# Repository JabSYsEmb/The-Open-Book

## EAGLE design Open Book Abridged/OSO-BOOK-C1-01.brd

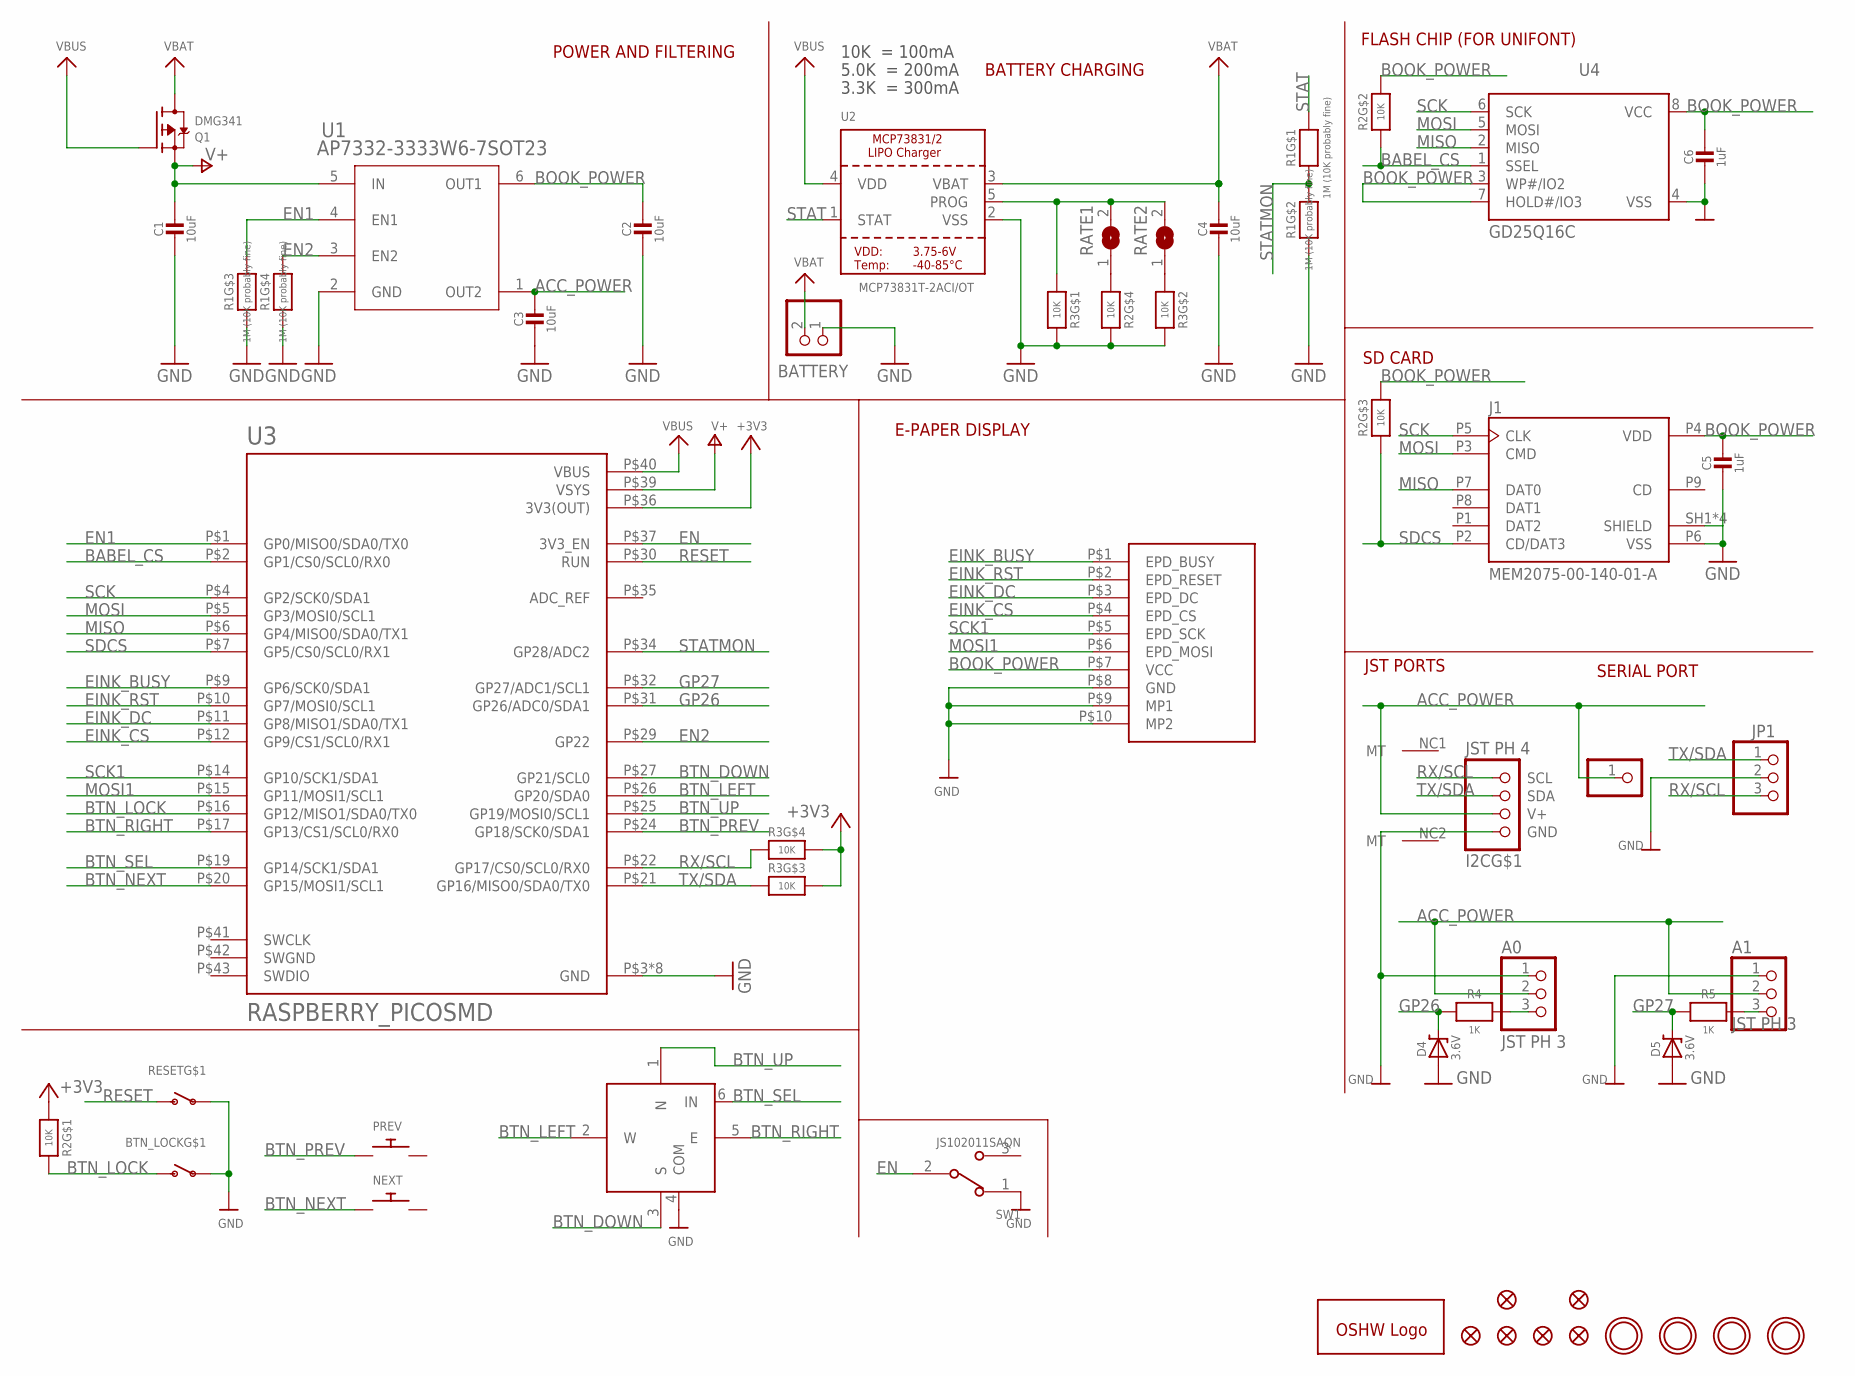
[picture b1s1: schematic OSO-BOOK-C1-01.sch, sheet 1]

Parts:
A0, A1: JST PH 3; JSTPH3
BATTERY: JSTPH; JSTPH2
BTN_LOCK: SWITCH_SPSTTL3330A; TL3330A
C1, C2, C3, C4: 10uF; 0805-NO
C5, C6: 1uF; 0805-NO
D4, D5: 3.6V; SOD-123
FID1, FID2, FID3, FID4, FID5, FID6: FIDUCIAL_1MM
GOLD_ORB_SM1: OSHWLOGOLOGO5MM; OSHW_5MM
I2C: JST PH 4; JSTPH4
J1: MEM2075-00-140-01-A; GCT_MEM2075-00-140-01-A
JP1: PINHD-1X3; 1X03
JP2: PINHD-1X1; 1X01
NEXT: SWITCH_PUSHBUTTON_3.5X6MM; TACTILE_3X6MM
PREV: SWITCH_PUSHBUTTON_3.5X6MM; TACTILE_3X6MM
Q1: DMG341; SOT23-R
R1: 1M (10K probably fine); EXBV8V
R2, R3: 10K; EXBV8V
R4, R5: 1K; 0805-NO
RATE1, RATE2: SOLDERJUMPER; SOLDERJUMPER_ARROW_NOPASTE
RESET: SWITCH_SPSTTL3330A; TL3330A
SW1: JS102011SAQN; SW_JS102011SAQN
SW2: NAVSWITCHSKQUABAUE010; SKQUBAE010
U1: AP7332-3333W6-7SOT23; SOT23-6
U2: MCP73831T-2ACI/OT; SOT23-5
U3: RASPBERRY_PICOSMD; PICO-PKG-SMD
U4: GD25Q16C; MICROBUILDER_SOIC8_150MIL
U$1, U$4, U$5, U$7: MOUNTINGHOLE2.5; MOUNTINGHOLE_2.5_PLATED
U$11: OSO-BOOK-C2-01

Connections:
+3V3: R2.1, R3.5 (2), R3.6 (2), U3.P$36 (3V3(OUT))
ACC_POWER: A0.2, A1.2, C3.1, I2C.2 (V+), JP2.1, U1.1 (OUT2)
BABEL_CS: R2.2 (1), U3.P$2 (GP1/CS0/SCL0/RX0), U4.1 (SSEL)
BOOK_POWER: C2.1, C5.1, C6.1, J1.P4 (VDD), R2.6 (2), R2.7 (2), U1.6 (OUT1), U4.3 (WP#/IO2), U4.7 (HOLD#/IO3), U4.8 (VCC), U$11.P$7 (VCC)
BTN_DOWN: SW2.3 (S), U3.P$27 (GP21/SCL0)
BTN_LEFT: SW2.2 (W), U3.P$26 (GP20/SDA0)
BTN_LOCK: BTN_LOCK.P$2 (S), R2.8 (2), U3.P$16 (GP12/MISO1/SDA0/TX0)
BTN_NEXT: NEXT.P$1, U3.P$20 (GP15/MOSI1/SCL1)
BTN_PREV: PREV.P$1, U3.P$24 (GP18/SCK0/SDA1)
BTN_RIGHT: SW2.5 (E), U3.P$17 (GP13/CS1/SCL0/RX0)
BTN_SEL: SW2.6 (IN), U3.P$19 (GP14/SCK1/SDA1)
BTN_UP: SW2.1 (N), U3.P$25 (GP19/MOSI0/SCL1)
EINK_BUSY: U3.P$9 (GP6/SCK0/SDA1), U$11.P$1 (EPD_BUSY)
EINK_CS: U3.P$12 (GP9/CS1/SCL0/RX1), U$11.P$4 (EPD_CS)
EINK_DC: U3.P$11 (GP8/MISO1/SDA0/TX1), U$11.P$3 (EPD_DC)
EINK_RST: U3.P$10 (GP7/MOSI0/SCL1), U$11.P$2 (EPD_RESET)
EN: SW1.2, U3.P$37 (3V3_EN)
EN1: R1.3 (1), U1.4 (EN1), U3.P$1 (GP0/MISO0/SDA0/TX0)
EN2: R1.4 (1), U1.3 (EN2), U3.P$29 (GP22)
GND: A0.1, A1.1, BATTERY.1, BTN_LOCK.P$1, C1.2, C2.2, C3.2, C4.2, C5.2, C6.2, D4.A, D5.A, I2C.1 (GND), J1.P6 (VSS), J1.SH1 (SHIELD), J1.SH2 (SHIELD), J1.SH3 (SHIELD), J1.SH4 (SHIELD), JP1.2, R1.2 (1), R1.5 (2), R1.6 (2), R2.5 (2), R3.7 (2), R3.8 (2), RESET.P$1, SW1.1, SW2.4 (COM), U1.2 (GND), U2.2 (VSS), U3.P$3 (GND), U3.P$8 (GND), U3.P$13 (GND), U3.P$18 (GND), U3.P$23 (GND), U3.P$28 (GND), U3.P$33 (GND), U3.P$38 (GND), U4.4 (VSS), U$11.P$8 (GND), U$11.P$9 (MP1), U$11.P$10 (MP2)
GP26: D4.C, R4.2, U3.P$31 (GP26/ADC0/SDA1)
GP27: D5.C, R5.2, U3.P$32 (GP27/ADC1/SCL1)
MISO: J1.P7 (DAT0), U3.P$6 (GP4/MISO0/SDA0/TX1), U4.2 (MISO)
MOSI: J1.P3 (CMD), U3.P$5 (GP3/MOSI0/SCL1), U4.5 (MOSI)
MOSI1: U3.P$15 (GP11/MOSI1/SCL1), U$11.P$6 (EPD_MOSI)
unnamed: R2.4 (1), RATE1.1
unnamed: R3.2 (1), RATE2.1
PROG: R3.1, RATE1.2, RATE2.2, U2.5 (PROG)
RESET: RESET.P$2 (S), U3.P$30 (RUN)
RX/SCL: I2C.4 (SCL), JP1.3, R3.4 (1), U3.P$22 (GP17/CS0/SCL0/RX0)
SCK: J1.P5 (CLK), U3.P$4 (GP2/SCK0/SDA1), U4.6 (SCK)
SCK1: U3.P$14 (GP10/SCK1/SDA1), U$11.P$5 (EPD_SCK)
SDCS: J1.P2 (CD/DAT3), R2.3 (1), U3.P$7 (GP5/CS0/SCL0/RX1)
STAT: R1.8 (2), U2.1 (STAT)
STATMON: R1.1, R1.7 (2), U3.P$34 (GP28/ADC2)
SWGND: U3.P$42 (SWGND)
TX/SDA: I2C.3 (SDA), JP1.1, R3.3 (1), U3.P$21 (GP16/MISO0/SDA0/TX0)
V+: C1.1, Q1.2 (S), U1.5 (IN), U3.P$39 (VSYS)
VBAT: BATTERY.2, C4.1, Q1.3 (D), U2.3 (VBAT)
VBUS: Q1.1 (G), U2.4 (VDD), U3.P$40 (VBUS)
_GP26: A0.3, R4.1
_GP27: A1.3, R5.1

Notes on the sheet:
POWER AND FILTERING
10K = 100mA
5.0K = 200mA
3.3K = 300mA
BATTERY CHARGING
FLASH CHIP (FOR UNIFONT)
SERIAL PORT
JST PORTS
SD CARD
E-PAPER DISPLAY

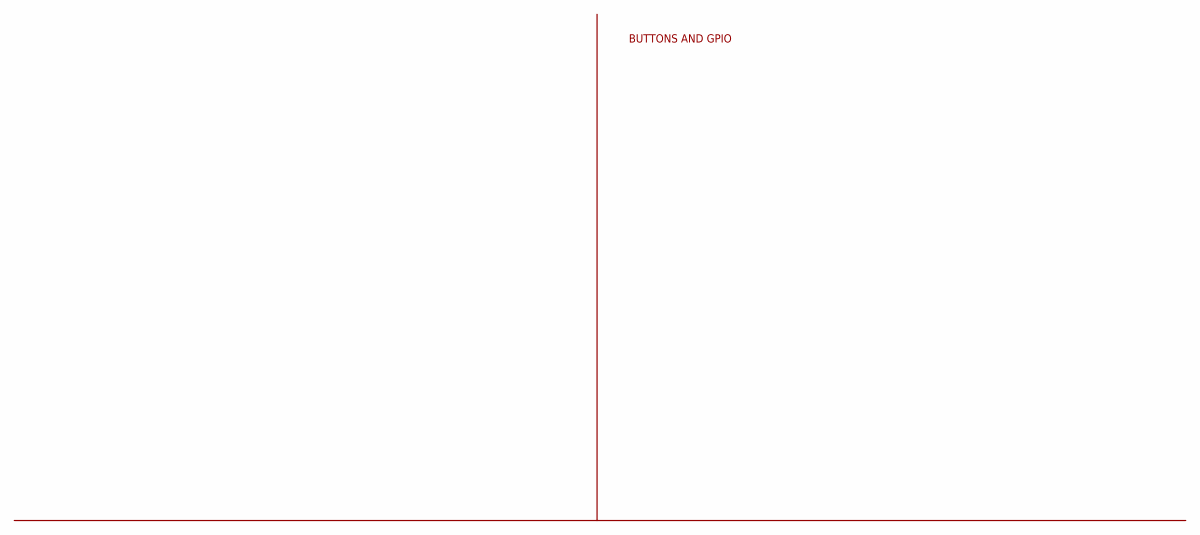
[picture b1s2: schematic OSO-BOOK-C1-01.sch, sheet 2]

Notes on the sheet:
BUTTONS AND GPIO

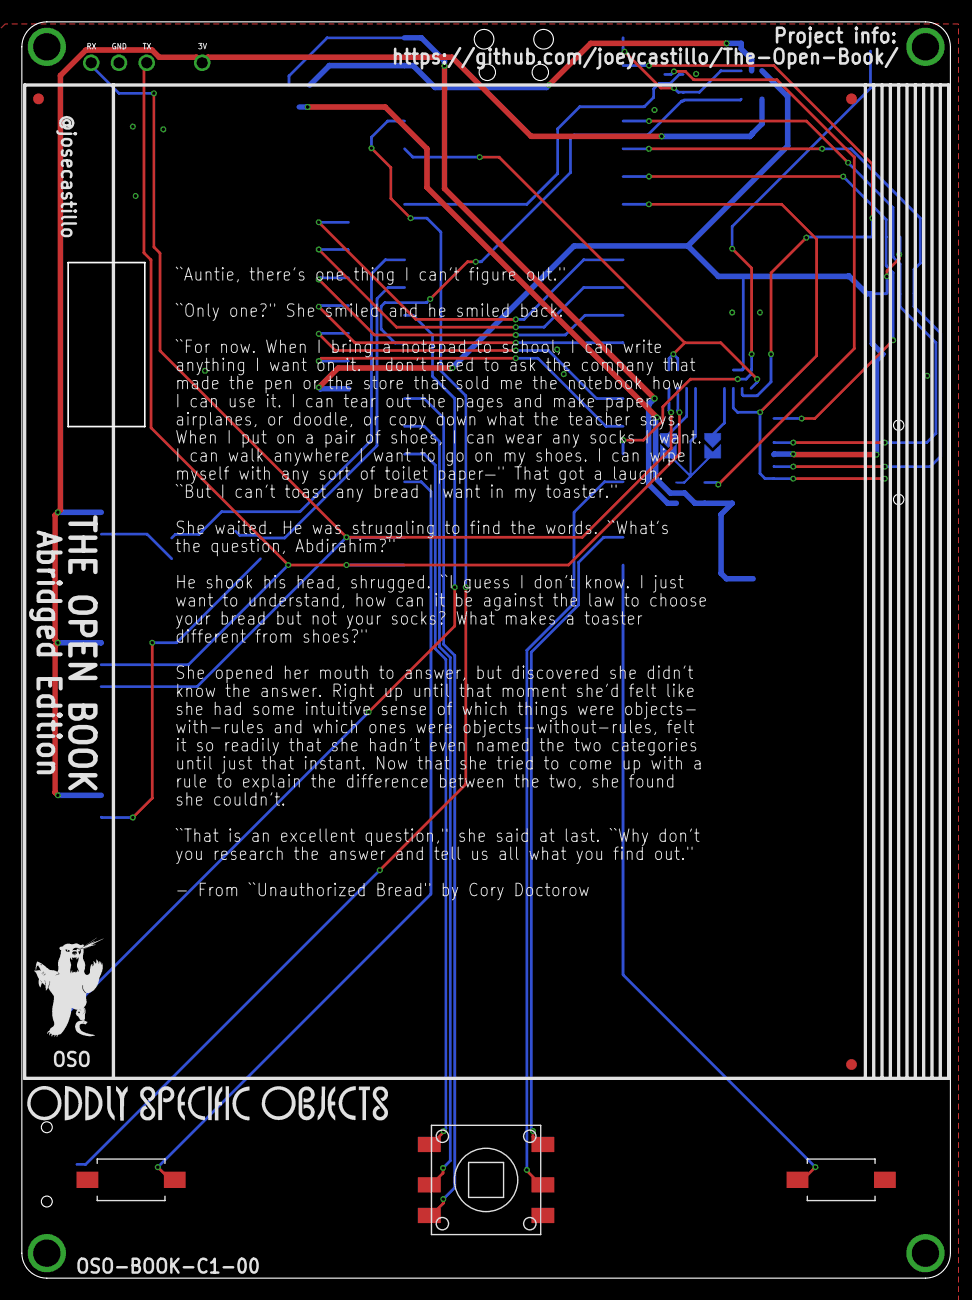
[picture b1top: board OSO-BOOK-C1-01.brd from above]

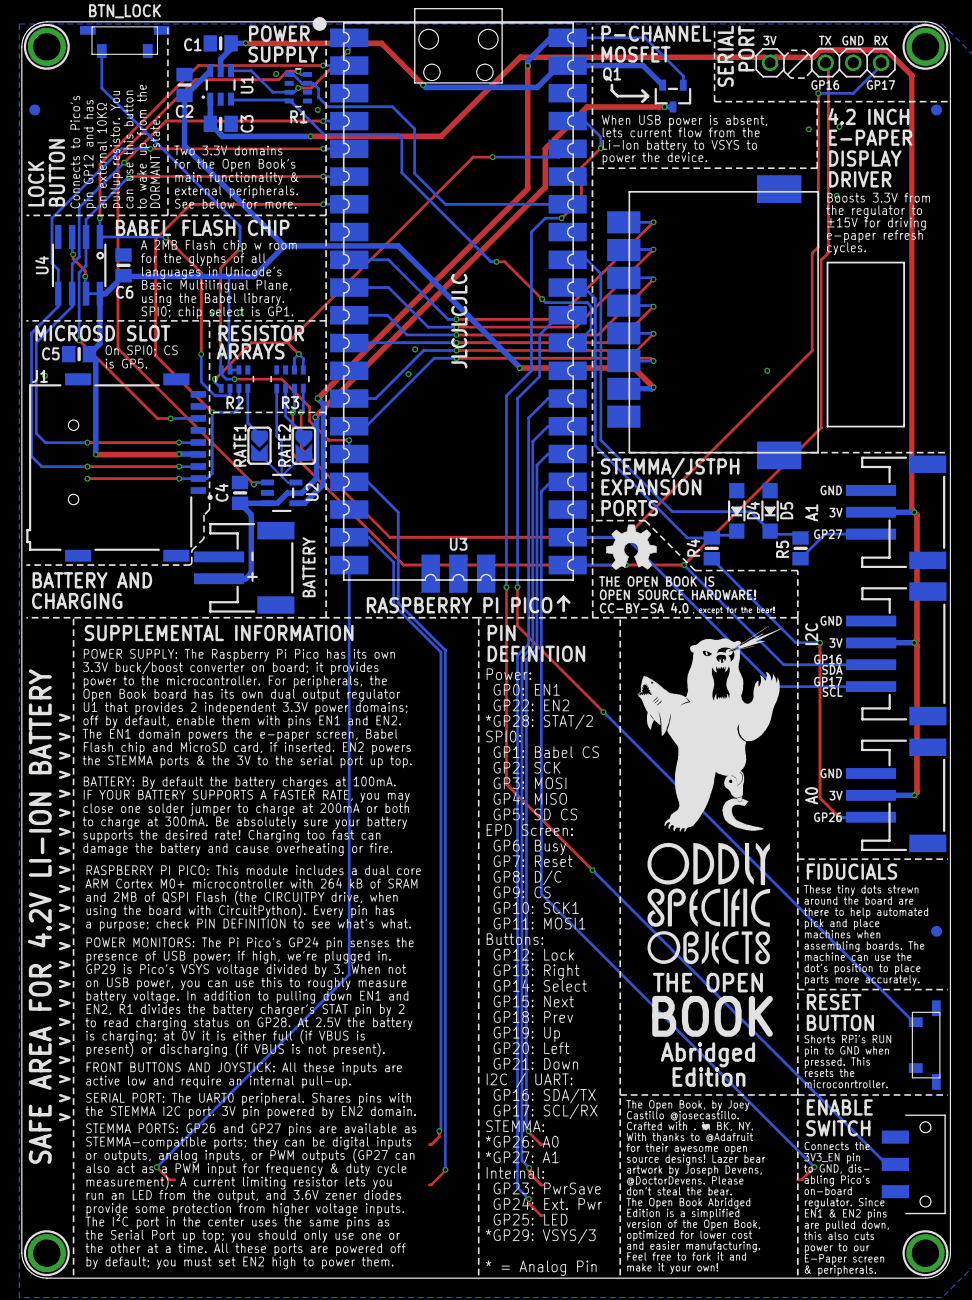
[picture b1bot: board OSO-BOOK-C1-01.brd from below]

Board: 2 copper layers, 85.0 x 115.0 mm, 49 parts (41 on the bottom side), 41 nets.

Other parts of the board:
U$45: OSO_WORDMARK_125X1300MIL_1000DPI
U$47: OSO_BEAR_525X750MIL_1000DPI
U$49: OSO_WORDMARK_THREELINE_450MIL_1000DPI
U$65: OSO_BEAR_250X360MIL_1000DPI

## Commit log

2021-05-23 open book abridged with castellated EPD driver

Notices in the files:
Open Book Abridged/OSO-BOOK-C1-01.brd:
CC-BY-SA 4.0
